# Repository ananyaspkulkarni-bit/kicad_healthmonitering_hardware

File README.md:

# CareBridge – Smart Health Companion
### ESP32-S3 Based Wearable Badge and Wristband

## Overview

CareBridge is a wearable health-companion project designed around a smart badge and wristband. The system explores the integration of embedded electronics, environmental sensing and GPS-based location tracking into a compact wearable solution.

The project aims to make essential environmental and location-related information more accessible through a portable, user-friendly device.

## Project Objectives

- Develop a compact wearable badge and wristband system.
- Integrate sensors and microcontrollers for data acquisition.
- Explore environmental monitoring through embedded sensors.
- Incorporate GPS-based location tracking.
- Design a practical hardware system with potential applications in personal safety and health monitoring.

## System Architecture

The project is organised into two wearable components:

### 1. Smart Badge

The badge is designed as the primary electronics unit, incorporating the microcontroller and supporting sensor modules.

Key hardware:
- ESP32-S3 microcontroller
- BME688 environmental sensor
- GPS module for location-related functionality

### 2. Smart Wristband

The wristband is designed as the complementary wearable component of the system.

Its role and electronics integration are part of the overall wearable system design.

## Hardware Components

| Component | Purpose |
|---|---|
| ESP32-S3 | Main microcontroller |
| BME688 | Environmental sensing |
| GPS Module | Location tracking |
| Smart Badge | Wearable electronics unit |
| Wristband | Complementary wearable unit |

## Tools and Technologies

- KiCad – Circuit schematic and PCB design
- ESP32-S3 – Embedded hardware platform
- Embedded C/C++ – Firmware development, where applicable
- Sensor interfacing and hardware integration

## Repository Structure

```text
CareBridge/
│
├── README.md
│
├── KiCad/
│   ├── project.kicad_pro
│   ├── project.kicad_sch
│   └── project.kicad_pcb
│
├── Images/
│   ├── badge-design.png
│   ├── wristband-design.png
│   └── pcb-3d-view.png
│
├── Documentation/
│   └── component-details.md
│
└── Firmware/
    └── source-code/
```

## Design and Development

The development process involves:

1. Identifying the functional requirements of the wearable system.
2. Selecting suitable microcontrollers and sensor modules.
3. Developing circuit schematics using KiCad.
4. Designing the PCB layout and organising component placement.
5. Exploring integration between the badge and wristband.
6. Developing and testing the embedded system.

## Current Project Status

The project involves the hardware design and development of a smart badge and wristband system. Individual implementation stages, including PCB design, firmware integration and hardware testing, are documented as development progresses.

## Future Scope

- Complete hardware integration of the badge and wristband.
- Expand sensor-based monitoring capabilities.
- Develop communication between wearable components.
- Improve power management and wearable form factor.
- Explore a companion application for displaying collected information.

## My Contribution

Worked on the hardware-oriented development of the wearable health-companion concept, including ESP32-S3 based system design, sensor integration considerations and PCB design using KiCad.

---

*Project: CareBridge – Smart Health Companion*  
*Platform: ESP32-S3 | Design Tool: KiCad*

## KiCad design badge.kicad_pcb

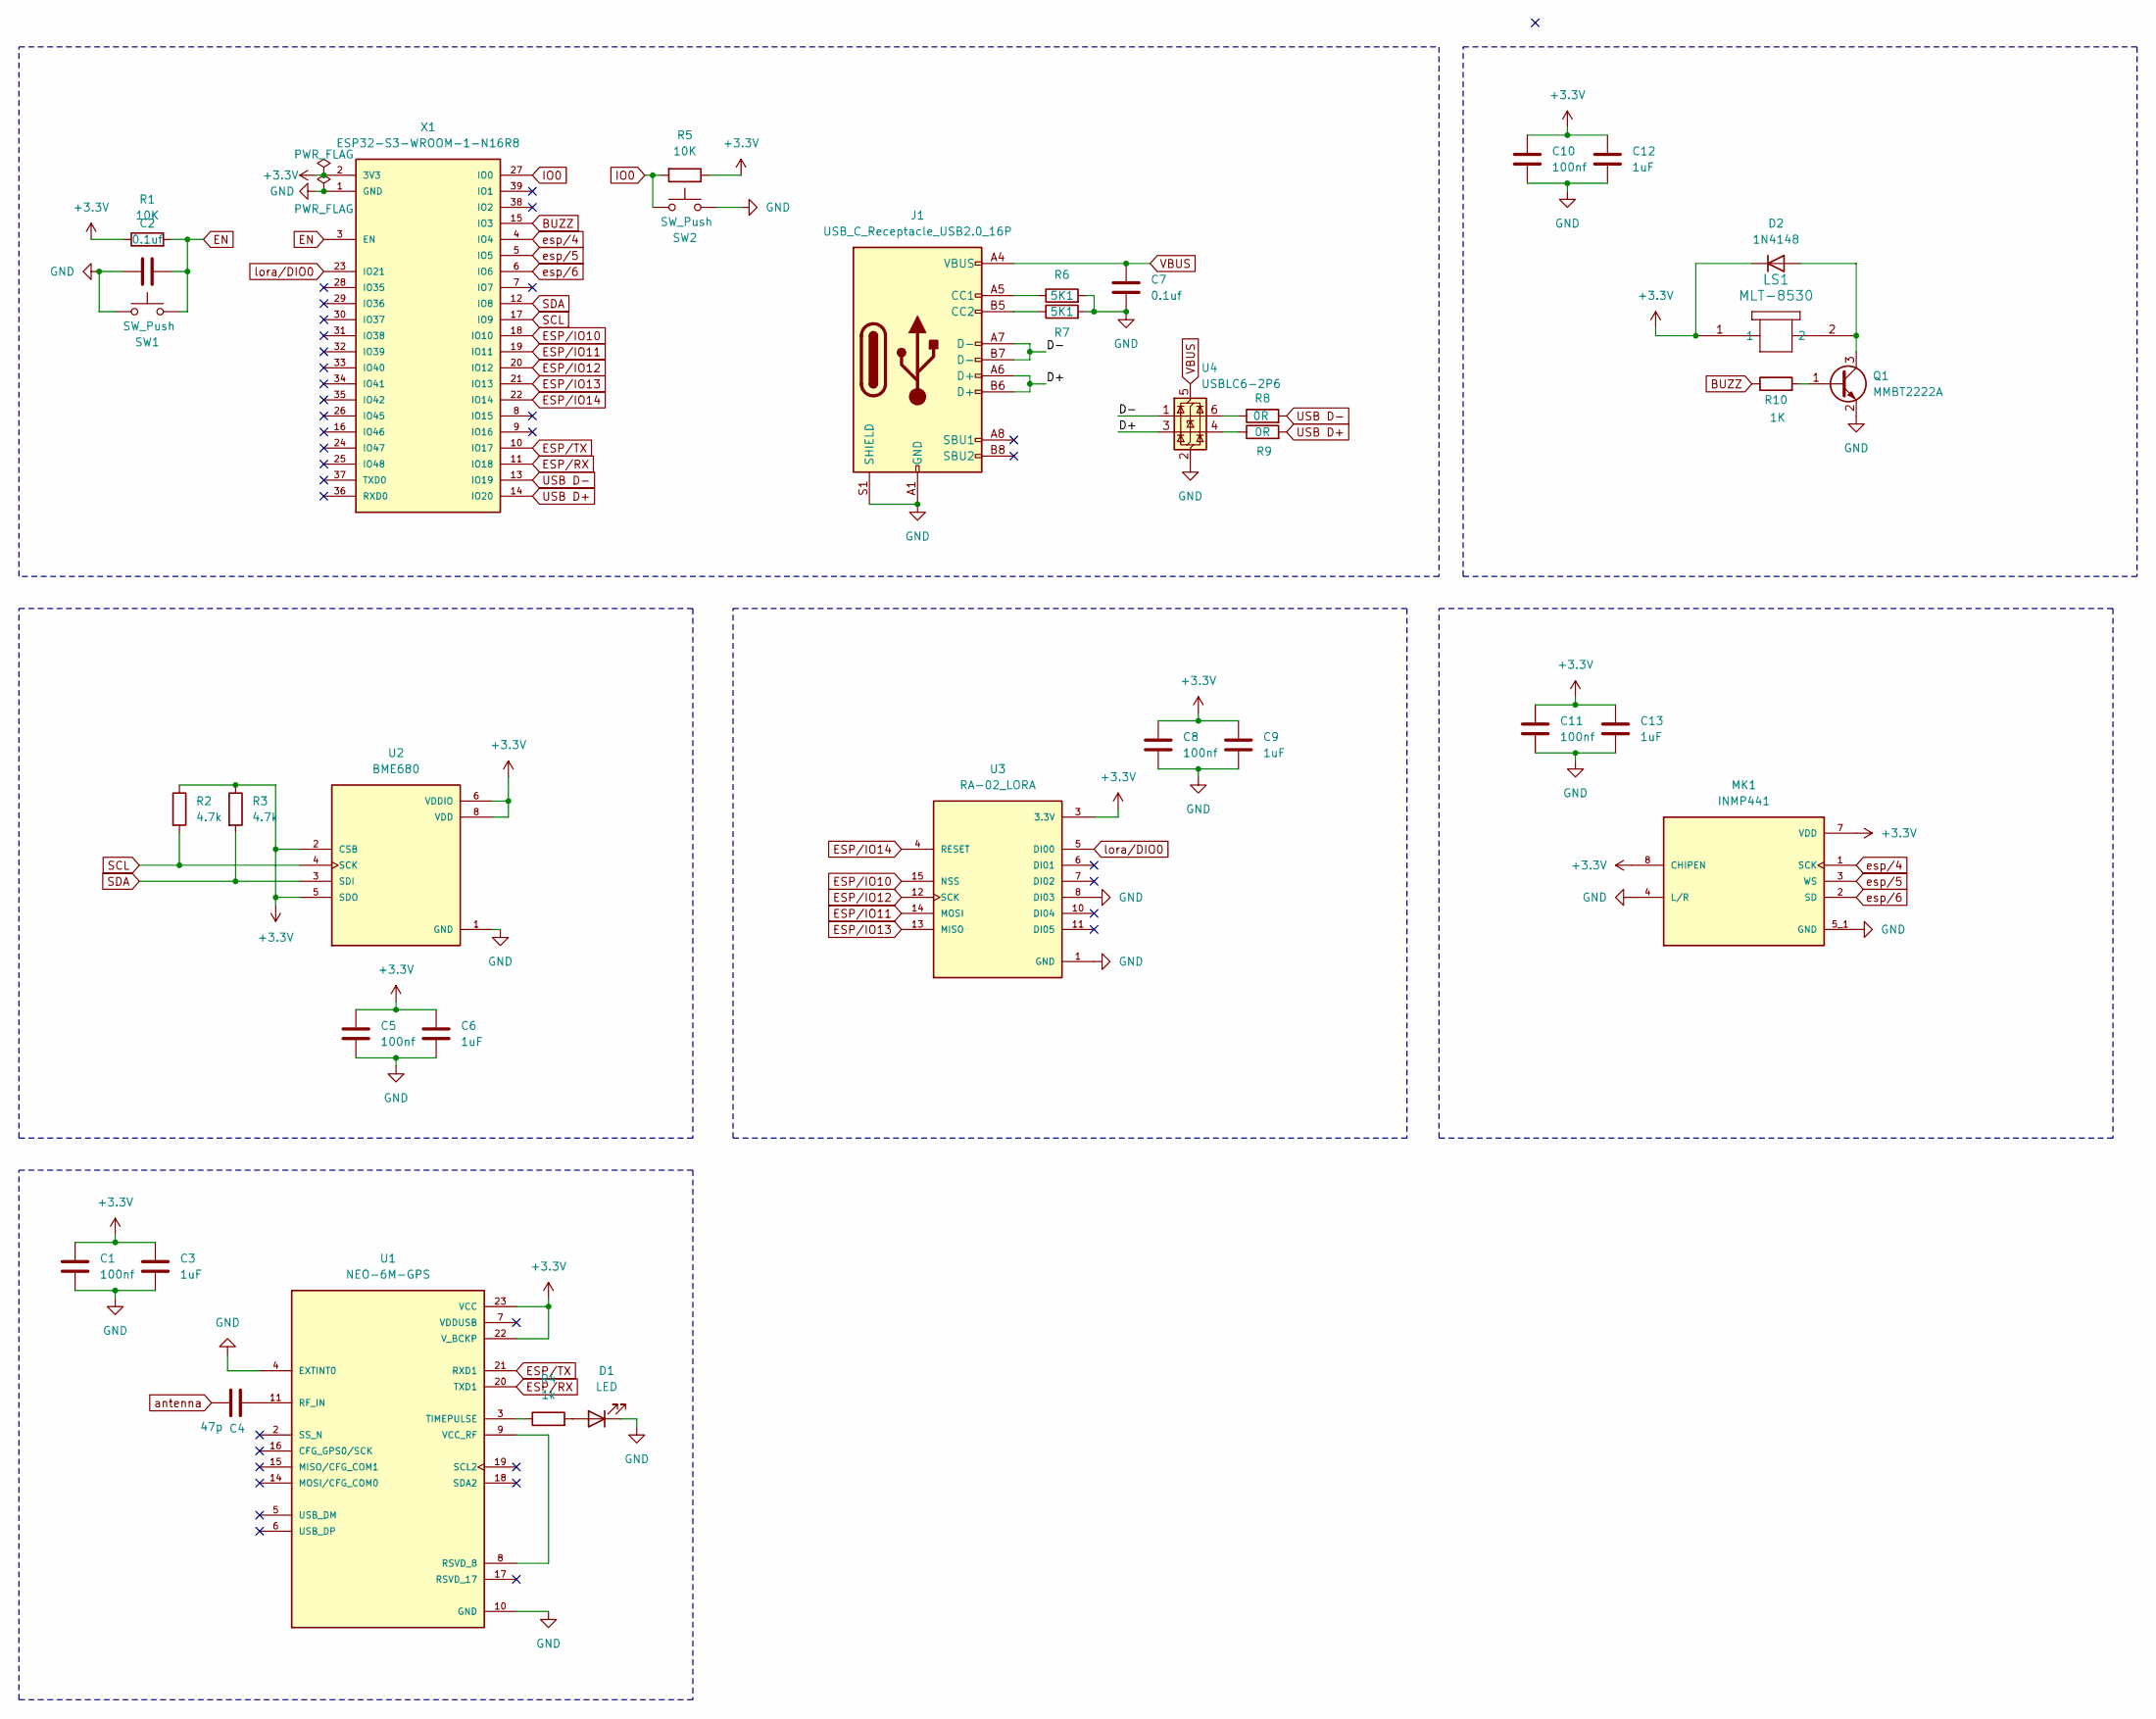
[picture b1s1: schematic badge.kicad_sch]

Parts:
C1, C5, C8, C10, C11: 100nf; C_0402_1005Metric
C2, C7: 0.1uf; C_0402_1005Metric
C3, C6, C9, C12, C13: 1uF; C_0603_1608Metric
C4: 47p; C_0402_1005Metric
D1: LED; LED_0402_1005Metric
D2: 1N4148; D_0402_1005Metric
J1: USB_C_Receptacle_USB2.0_16P; USB_C_Receptacle_G-Switch_GT-USB-7010ASV
LS1: MLT-8530; MLT-8530_JHE
MK1: INMP441; MIC_INMP441; PARTREV 1.1
Q1: MMBT2222A; SOT-23
R1, R5: 10K; R_0402_1005Metric
R2, R3: 4.7k; R_0402_1005Metric
R4: 1k; R_0402_1005Metric
R6, R7: 5K1; R_0402_1005Metric
R8, R9: 0R; R_0402_1005Metric
R10: 1K; R_0402_1005Metric
SW1, SW2: SW_Push; Panasonic_EVQPUJ_EVQPUA
U1: NEO-6M-GPS; XCVR_NEO-6M-GPS; PARTREV R15
U2: BME680; PSON80P300X300X100-8N; PARTREV 1.9
U3: RA-02_LORA; MODULE_RA-02_LORA; PARTREV 2018/03/02
U4: USBLC6-2P6; SOT-666
X1: ESP32-S3-WROOM-1-N16R8; ESP32-S3-WROOM-1_EXP; MANUFACTURER_PART_NUMBER ESP32-S3-WROOM-1-N16R8

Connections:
+3.3V: C1.1, C3.1, C5.1, C6.1, C8.1, C9.1, C10.1, C11.1, C12.1, C13.1, D2.1 (K), LS1.1, MK1.7 (VDD), MK1.8 (CHIPEN), R1.1, R2.1, R3.1, R5.1, U1.22 (V_BCKP), U1.23 (VCC), U2.2 (CSB), U2.5 (SDO), U2.6 (VDDIO), U2.8 (VDD), U3.3 (3.3V), X1.2 (3V3)
/D+: J1.A6 (D+), J1.B6 (D+), U4.3 (I/O2)
/D-: J1.A7 (D-), J1.B7 (D-), U4.1 (I/O1)
BUZZ: R10.1, X1.15 (IO3)
EN: C2.2, R1.2, SW1.2, X1.3 (EN)
ESP/IO10: U3.15 (NSS), X1.18 (IO10)
ESP/IO11: U3.14 (MOSI), X1.19 (IO11)
ESP/IO12: U3.12 (SCK), X1.20 (IO12)
ESP/IO13: U3.13 (MISO), X1.21 (IO13)
ESP/IO14: U3.4 (RESET), X1.22 (IO14)
ESP/RX: U1.20 (TXD1), X1.11 (IO18)
ESP/TX: U1.21 (RXD1), X1.10 (IO17)
GND: C1.2, C2.1, C3.2, C5.2, C6.2, C7.2, C8.2, C9.2, C10.2, C11.2, C12.2, C13.2, D1.1 (K), J1.A1 (GND), J1.A12 (GND), J1.B1 (GND), J1.B12 (GND), J1.S1 (SHIELD), MK1.4 (L/R), MK1.5_1 (GND), MK1.5_2 (GND), MK1.6 (GND), MK1.9 (GND), Q1.2 (E), R6.2, R7.2, SW1.1, SW2.2, U1.4 (EXTINT0), U1.10 (GND), U1.12 (GND), U1.13 (GND), U1.24 (GND), U2.1 (GND), U2.7 (GND), U3.1 (GND), U3.2 (GND), U3.8 (DI03), U3.9 (GND), U3.16 (GND), U4.2 (GND), X1.1 (GND), X1.40 (GND), X1.41 (GND), X1.42 (GND), X1.43 (GND), X1.44 (GND), X1.45 (GND), X1.46 (GND), X1.47 (GND), X1.48 (GND), X1.49 (GND)
IO0: R5.2, SW2.1, X1.27 (IO0)
unnamed: D1.2 (A), R4.2
unnamed: D2.2 (A), LS1.2, Q1.3 (C)
unnamed: J1.A5 (CC1), R6.1
unnamed: J1.B5 (CC2), R7.1
unnamed: Q1.1 (B), R10.2
unnamed: R8.1, U4.6 (I/O1)
unnamed: R9.1, U4.4 (I/O2)
unnamed: C4.1, U1.11 (RF_IN)
unnamed: U1.8 (RSVD_8), U1.9 (VCC_RF)
unnamed: R4.1, U1.3 (TIMEPULSE)
SCL: R2.2, U2.4 (SCK), X1.17 (IO9)
SDA: R3.2, U2.3 (SDI), X1.12 (IO8)
USB D+: R9.2, X1.14 (IO20)
USB D-: R8.2, X1.13 (IO19)
VBUS: C7.1, J1.A4 (VBUS), J1.A9 (VBUS), J1.B4 (VBUS), J1.B9 (VBUS), U4.5 (VBUS)
antenna: C4.2
esp/4: MK1.1 (SCK), X1.4 (IO4)
esp/5: MK1.3 (WS), X1.5 (IO5)
esp/6: MK1.2 (SD), X1.6 (IO6)
lora/DIO0: U3.5 (DI00), X1.23 (IO21)

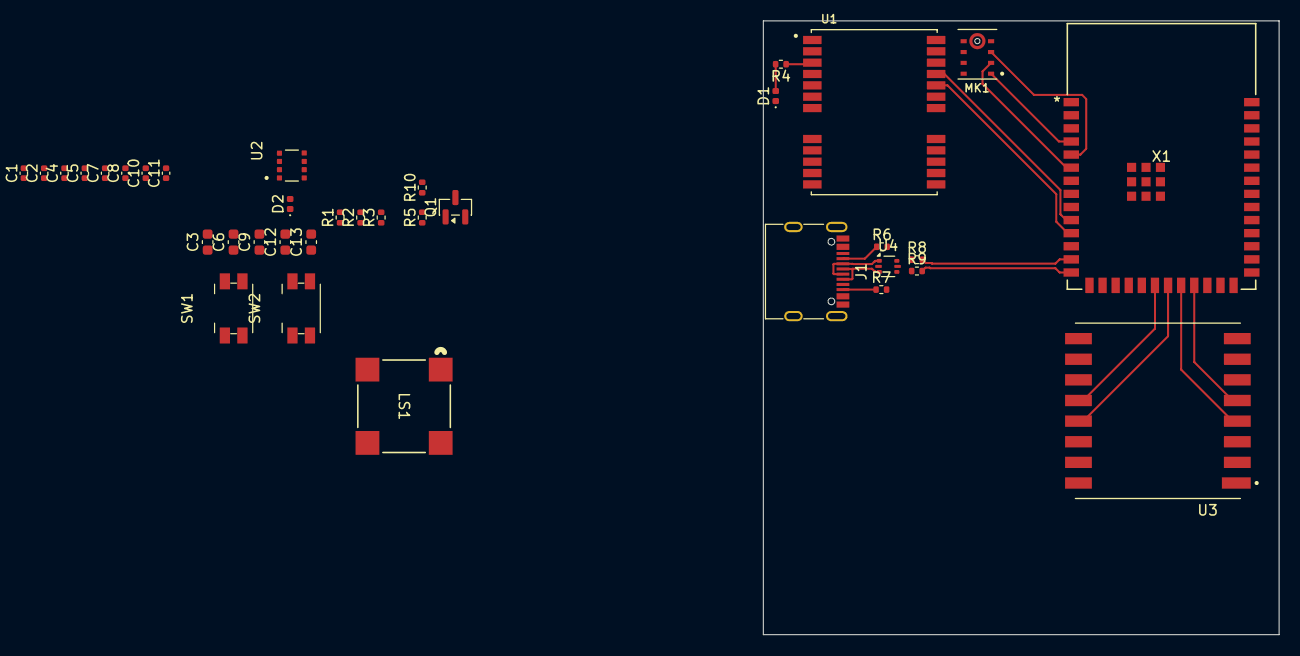
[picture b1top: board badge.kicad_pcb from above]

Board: 2 copper layers, 50.0 x 59.5 mm, 36 parts (0 on the bottom side), 33 nets.
